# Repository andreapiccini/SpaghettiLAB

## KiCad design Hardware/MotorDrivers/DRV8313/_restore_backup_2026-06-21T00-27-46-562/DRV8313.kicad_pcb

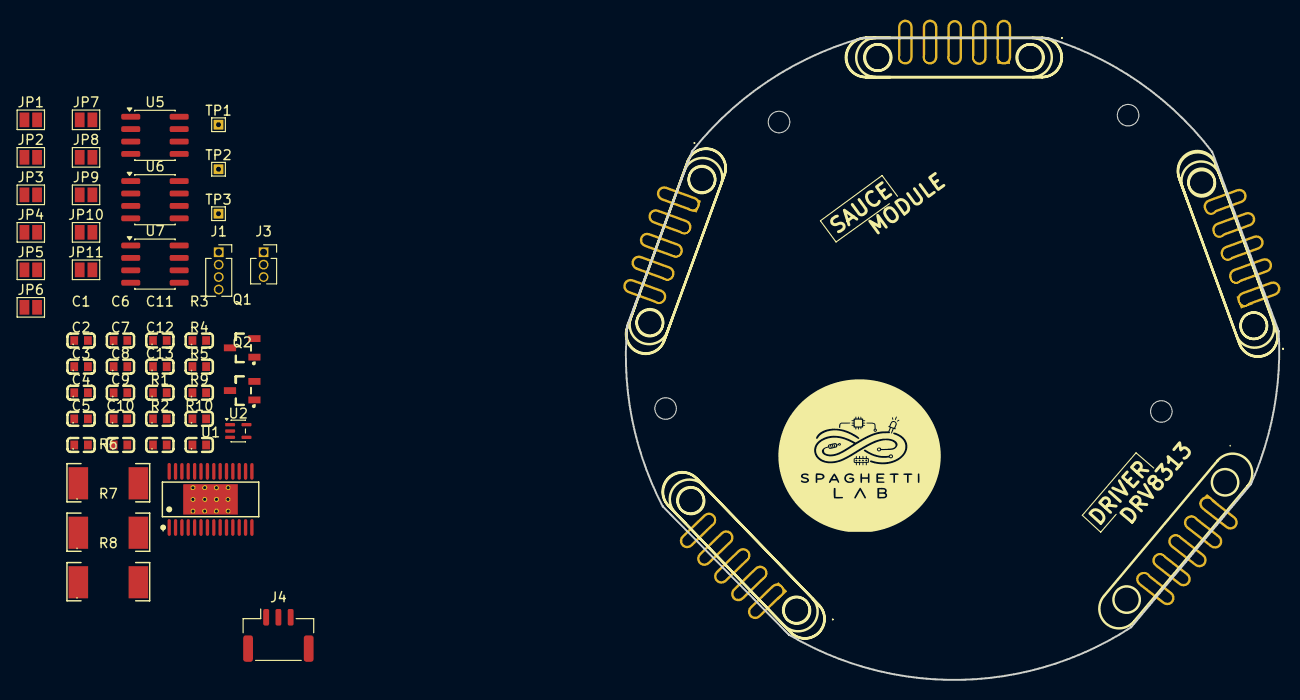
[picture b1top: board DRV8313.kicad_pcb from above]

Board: 2 copper layers, 66.8 x 65.6 mm, 61 parts (1 on the bottom side), 42 nets, no tracks yet.

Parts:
C1: 10nF; C0603
C2, C5, C6, C7, C8, C9, C11, C12, C13: 100nF; C0603
C3: 470nF; C0603
C4: 10uF; C0603
C10: 1uF; C0603
CN7, CN8, CN9, CN10, CN11: PR5L4015-5P-C-F; CONN-TH_PR5L4015-5P-C-F
H1, H2, H3, H4: MountingHole; MountingHole_2.2mm_M2
J1: Conn_01x04_Socket; PinSocket_1x04_P1.27mm_Vertical
J3: Conn_01x02_Socket; PinSocket_1x03_P1.27mm_Vertical
J4: Conn_01x03_Socket; JST_GH_SM03B-GHS-TB_1x03-1MP_P1.25mm_Horizontal
JP1, JP2: Jumper_2_Open; SolderJumper-2_P1.3mm_Open_Pad1.0x1.5mm
JP3, JP4, JP5, JP6, JP7, JP8, JP9, JP10, JP11: SolderJumper_2_Open; SolderJumper-2_P1.3mm_Open_Pad1.0x1.5mm
Q1, Q2: BSS123_C427379; SOT-23-3_L2.9-W1.5-P1.90-LS2.6-BR
R1, R2, R3, R4, R5, R10: 10k; C0603
R6, R7, R8: 10m; RES-SMD_L6.4-W3.2-R2512
R9: 1k; C0603
TP1, TP2, TP3: TestPoint_Flag; TestPoint_THTPad_1.0x1.0mm_Drill0.5mm
U1: MS8313; HTSSOP-28_L9.7-W4.4-P0.65-LS6.4-BL-EP
U2: TLV9001IDCK; SOT-353_SC-70-5
U5, U6, U7: INA241A2xD; SOIC-8_3.9x4.9mm_P1.27mm
U35, U36, U37, U38, U39: PR5L5015-5P-C-H; CONN-TH_PR5L5015-5P-C-H

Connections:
5V: CN8.5, U35.5
+3.3V: C3.2, JP4.2 (B), R1.1, R3.2, R4.2, R5.2, R10.2, U1.15 (V3P3OUT), U2.5 (V+)
/FLEX0: CN10.2, JP8.1 (A), U37.2
/FLEX1: CN10.3, JP9.1 (A), U37.3
/FLEX2: CN7.1, JP10.1 (A), U38.1
/FLEX3: CN7.2, JP5.1 (A), U38.2
/FLEX4: CN7.3, JP6.1 (A), U38.3
/FLEX5: CN9.1, JP7.1 (A), U36.1
/FLEX6: CN11.4, JP11.1 (A), U39.4
/ID: CN10.1, U37.1
/OUT_SENSE1: R6.1, TP1.1 (1_1), U1.5 (OUT1), U5.8 (+)
/OUT_SENSE2: R7.1, TP2.1 (1_1), U1.8 (OUT2), U6.8 (+)
/OUT_SENSE3: R8.1, TP3.1 (1_1), U1.9 (OUT3), U7.8 (+)
/REF: C10.1, JP1.2 (B), JP2.1 (A), R1.2, R2.1, U2.1 (+)
/REF_B: C11.1, C12.1, C13.1, J3.1, JP2.2 (B), U2.3 (-), U2.4, U5.3 (REF2), U5.7 (REF1), U6.3 (REF2), U6.7 (REF1), U7.3 (REF2), U7.7 (REF1)
/SCL_AUX: CN8.3, U35.3
/SDA_AUX: CN8.4, U35.4
/~INT: CN9.2, U36.2
/~RESET: CN9.3, Q1.1 (G), U36.3
C_SENSE1: JP5.2 (B), U5.5
C_SENSE2: JP6.2 (B), U6.5
C_SENSE3: JP7.2 (B), U7.5
EN: JP11.2 (B), R9.2
GND: C3.1, C4.2, C5.2, C6.1, C7.1, C8.1, C9.1, C10.2, C11.2, C12.2, C13.2, CN7.5, CN8.2, CN9.5, CN10.5, CN11.2, J1.4, J3.2, JP1.1 (A), Q1.2 (S), Q2.2 (S), R2.2, U1.6 (PGND1), U1.7 (PGND2), U1.10 (PGND3), U1.12 (COMPP), U1.13 (COMPN), U1.14 (GND), U1.19 (nCOMP0), U1.20 (GND), U1.21 (NC), U1.28 (GND), U1.29 (EP), U2.2 (V-), U5.2 (GND), U5.4 (GND), U6.2 (GND), U6.4 (GND), U7.2 (GND), U7.4 (GND), U35.2, U36.5, U37.5, U38.5, U39.2
IN1: JP8.2 (B), U1.27 (IN1)
IN2: JP9.2 (B), U1.25 (IN2)
IN3: JP10.2 (B), U1.23 (IN3)
unnamed: Q1.3 (D), Q2.1 (G), R10.1
unnamed: C1.2, U1.1 (CP1)
unnamed: C1.1, U1.2 (CP2)
unnamed: R9.1, U1.22 (EN3), U1.24 (EN2), U1.26 (EN1)
unnamed: C2.2, U1.3 (VCP)
OUT1: J4.1, R6.2, U5.1 (-)
OUT2: J4.2, R7.2, U6.1 (-)
OUT3: J4.3, R8.2, U7.1 (-)
VCC: C2.1, C4.1, C5.1, C6.2, C7.2, C8.2, C9.2, JP3.2 (B), U1.4 (VM), U1.11 (VM), U5.6 (V+), U6.6 (V+), U7.6 (V+)
VEXT: CN7.4, CN8.1, CN9.4, CN10.4, CN11.1, JP3.1 (A), U35.1, U36.4, U37.4, U38.4, U39.1
VHV: CN11.5, U39.5
VLOGIC: CN11.3, JP4.1 (A), U39.3
nFAULT: J1.3, R5.1, U1.18 (nFAULT)
nRESET: J1.1, Q2.3 (D), R3.1, U1.16 (nRESET)
nSLEEP: J1.2, R4.1, U1.17 (nSLEEP)

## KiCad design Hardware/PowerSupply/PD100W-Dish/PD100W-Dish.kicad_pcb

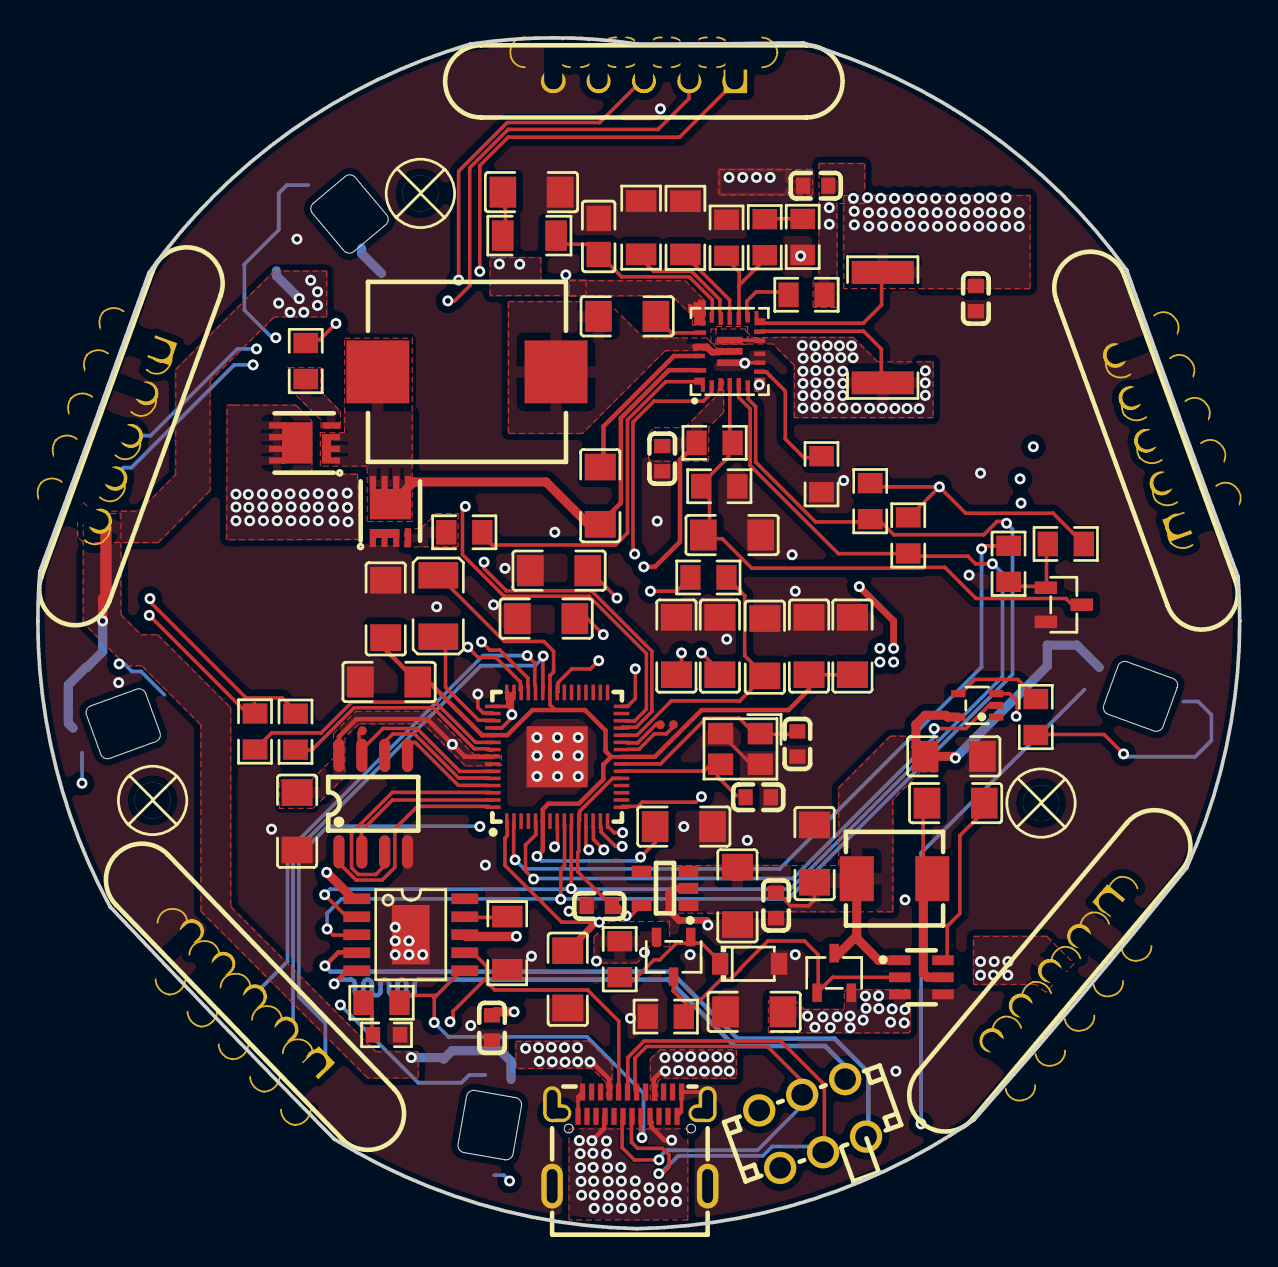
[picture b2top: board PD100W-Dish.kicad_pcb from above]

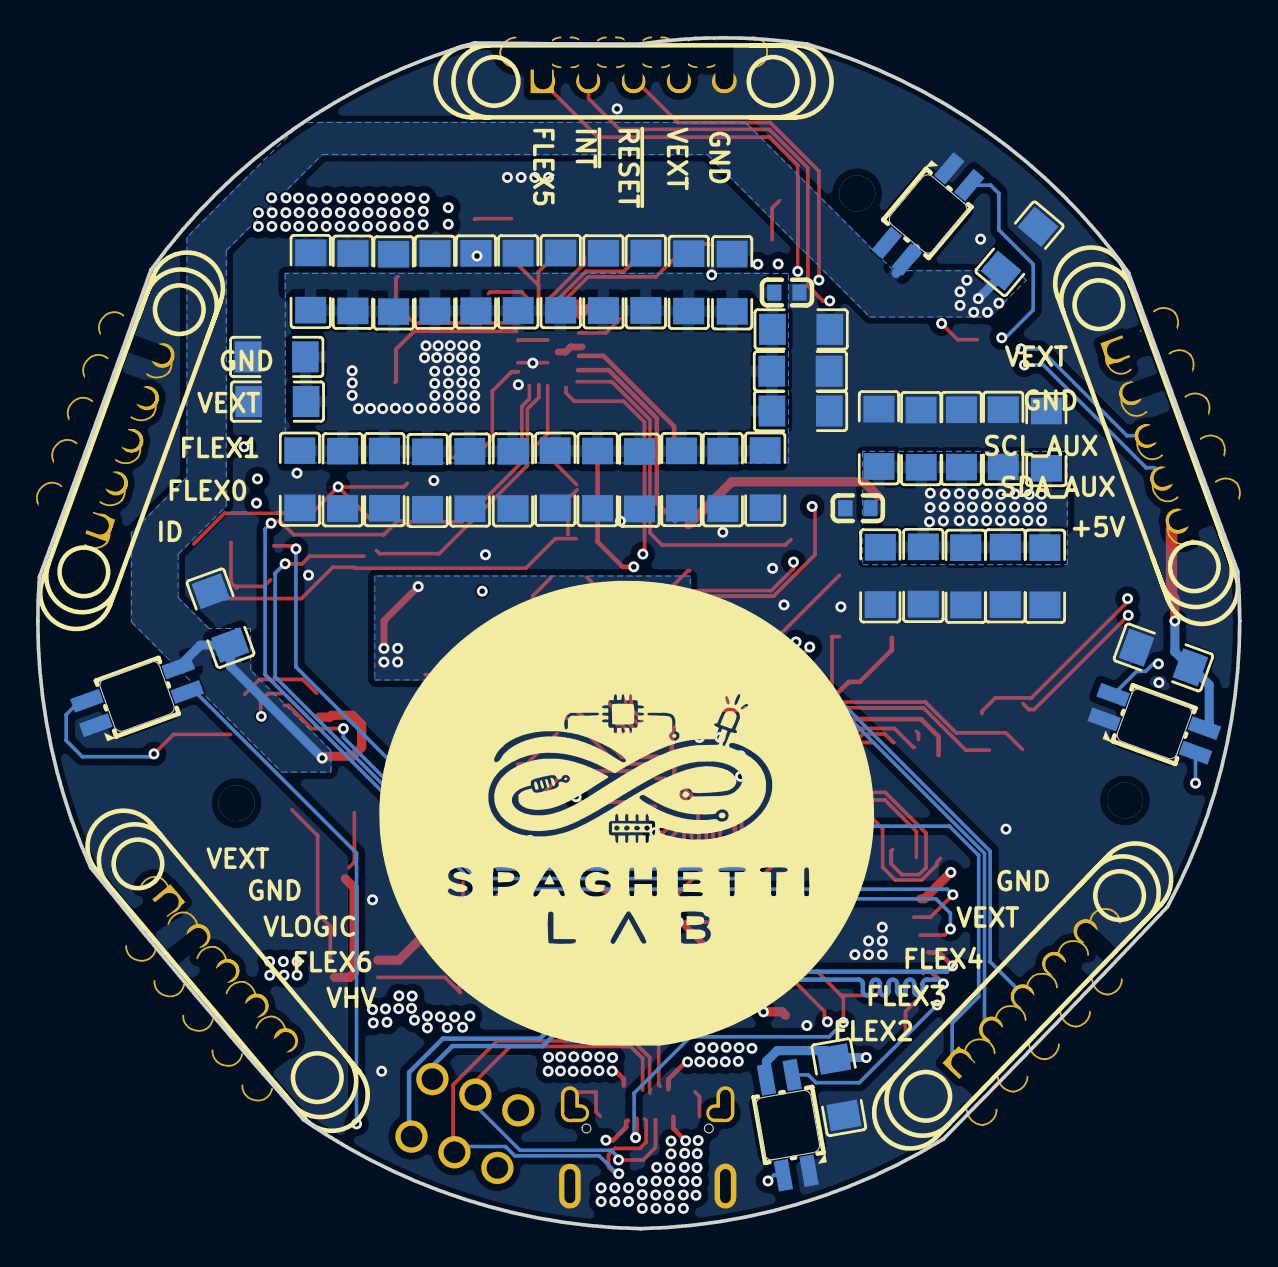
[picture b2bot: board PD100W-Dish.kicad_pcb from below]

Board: 4 copper layers, 66.8 x 66.2 mm, 139 parts (53 on the bottom side), 75 nets.

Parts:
C1, C2, C3, C4, C5, C6, C7, C8, C9, C10, C11, C12, C13, C14, C15, C16, C17, C25, C26, C27, C28, C29, C30, C32, C33, C40, C42, C54, C56, C57, C58, C61, C62, C67, C68, C70, C71, C72, C73, C74, C76, C81, C82, C87, C88, C89, C90, C91, C92, C93, C94, C95, C96, C97, C98, C99, C100, C101, C102, C103, C104, C109, C110: C1206
C24, C34, C35, C36, C37, C38, C43, C44, C65, C66: C0603
C41: C0805
CN7, CN8, CN9, CN10, CN11: CONN-TH_PR5L4015-5P-C-F
D1: SOD-123_L2.7-W1.6-LS3.7-RD
L4: L1210
L5: IND-SMD_L11.0-W10.0
L7: IND-SMD_L5.4-W5.2_FXL05XX
LED1, LED2, LED7, LED8: LED-SMD_4P-L3.2-W2.8-LS5.9_SK6812MINI-E
Q3: SOT-23-3_L2.9-W1.3-P1.90-LS2.4-BR
Q4, Q5: SOT-23-3_L3.0-W1.7-P0.95-LS2.9-BR
R20, R29, R30, R31, R32, R33, R34, R35, R36, R37, R38, R39, R40, R44, R45, R48, R49, R60, R61, R64: R0805
R21, R25, R26, R27: R1206
R46: R2512
R47: R0603
SCREW1, SCREW3, SCREW4: Screw-Hole-M2
SW1: SW-TH_K3-2245D-F1
TP1, TP2, TP4: Test-Point-0.5mm
U7: VQFN-HR-26_L4.0-W3.5_TPS55288RPMR
U8, U9: TSDSON-8-FL_L3.3-W3.3-P0.65-BL
U15: TSOT-23-6_L2.9-W1.6-P0.95-LS2.8-BL
U16: SOT-25-5_L2.9-W1.6-P0.95-LS2.8-BL
U17: QFN-60_L7.0-W7.0-P0.40-TL-EP3.4
U19: SOP-8_L4.9-W3.9-P1.27-LS6.0-BL
U33: SOT-353_L2.2-W1.4-P0.65-LS2.4-BR
U35, U36, U37, U38, U39: CONN-TH_PR5L5015-5P-C-H
U40: ESSOP-10_L4.9-W3.9-P1.0-LS6.0-TL-EP
USB4: USB-C-SMD_TYPEC-324G-BCP24
X1: CRYSTAL-SMD_4P-L3.2-W2.5-BL

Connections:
1V1: C70.1, C71.1, C72.1, C73.1, C74.1, L4.2, U17.6, U17.23, U17.39, U17.50
5V: C65.2, C81.2, C82.2, C102.1, C103.1, C104.1, C109.1, C110.1, CN8.5, L7.2, LED1.3, LED2.3, LED7.3, LED8.3, Q4.3, U15.1, U16.1, U16.3, U33.5, U35.5
$1N8973: R45.1, U7.2
$1N8976: R45.2, U8.4
$1N8978: R44.2, U9.4
$1N8980: R44.1, U7.1
$1N9027: C32.1, U7.20
$1N9029: C40.1, U7.22
$1N9105: R25.2, U7.16
$1N9112: R26.2, U7.17
$1N9115: C41.2, R27.2, U7.18
$1N9120: C42.2, R27.1
$1N9155: R30.2, U7.8
$1N9158: C33.2, Q3.3, R31.1, R32.2, U7.4
$1N9180: Q3.1, R33.1, R34.1
$1N24858: R29.2, U7.14
$1N24894: R20.1, R60.2
$1N24900: R20.2, R38.2, U7.15
$2N2987: TP1.1, U17.25
$2N2988: TP2.1, U17.24
$2N2989: C57.1, R37.1, U17.26
$2N2992: C44.1, U17.22, X1.1
$2N2993: C43.1, U17.21, X1.3
$2N3073: R39.1, U17.52
$2N3074: R40.1, U17.51
$2N3076: L4.1, U17.48
$2N5930: LED7.4, LED8.2
$2N6872: R61.2, U33.4
$2N6876: LED7.2, R61.1
$2N14399: LED2.2, LED8.4
$2N14400: LED1.2, LED2.4
$3N1781: R21.1, U40.9
$3N1785: C62.2, U15.6
$3N1787: C62.1, L7.1, U15.5
$3N1801: R47.2, R64.1
$3N1804: Q4.1, Q5.3, R48.1, U15.2
$3N1806: D1.1, Q5.1, R49.2
ADD_LED: U17.5, U33.2
AGND: C1.1, C2.1, C3.1, C4.1, C5.1, C6.1, C7.1, C8.1, C9.1, C10.1, C11.1, C12.1, C13.1, C14.1, C15.1, C16.1, C17.1, C24.1, C25.1, C26.1, C27.2, C28.2, C29.2, C30.2, C33.1, C34.1, C35.1, C36.1, C37.1, C38.1, C41.1, C42.1, C43.2, C44.2, C54.1, C56.1, C57.2, C58.1, C61.1, C65.1, C66.1, C67.1, C68.1, C70.2, C71.2, C72.2, C73.2, C74.2, C76.2, C81.1, C82.1, C87.1, C88.1, C89.1, C90.1, C91.1, C92.1, C93.1, C94.1, C95.1, C96.1, C97.1, C98.1, C99.1, C100.1, C101.1, C102.2, C103.2, C104.2, C109.2, C110.2, CN7.5, CN8.2, CN9.5, CN10.5, CN11.2, D1.2, LED1.1, LED2.1, LED7.1, LED8.1, Q3.2, R21.2, R25.1, R26.1, R30.1, R32.1, R38.1, R47.1, R48.2, R60.1, U7.7, U7.9, U7.10, U7.24, U9.1, U9.2, U9.3, U15.4, U16.2, U17.47, U17.61, U19.4, U33.3, U35.2, U36.5, U37.5, U38.5, U39.2, U40.11, USB4.1, USB4.2, USB4.3, USB4.4, USB4.A1, USB4.A12, USB4.B1, USB4.B12, X1.2, X1.4
EN_PSOUT: R34.2, U17.2
FLEX0: CN10.2, U17.14, U37.2
FLEX1: CN10.3, U17.15, U37.3
FLEX2: CN7.1, U17.43, U38.1
FLEX3: CN7.2, U17.40, U38.2
FLEX4: CN7.3, U17.41, U38.3
FLEX5: CN9.1, U17.42, U36.1
FLEX6: CN11.4, U17.16, U39.4
ID: CN10.1, U17.13, U37.1
INT_N: CN9.2, U17.8, U36.2
IOSN+2: C1.2, C2.2, C3.2, C4.2, C5.2, C6.2, C7.2, C8.2, C9.2, C10.2, C11.2, C12.2, C27.1, C28.1, C29.1, C30.1, C35.2, C87.2, C88.2, C89.2, C90.2, C91.2, C92.2, C93.2, C94.2, C95.2, C96.2, C97.2, C98.2, R46.1, U7.11, U7.12, U7.26
QSPI_SCLK: U17.56, U19.6
QSPI_SD0: U17.57, U19.5
QSPI_SD1: U17.59, U19.2
QSPI_SD2: U17.58, U19.3
QSPI_SD3: TP4.1, U17.55, U19.7
QSPI_SS: U17.60, U19.1
RESET_N: CN9.3, U17.12, U36.3
SCL_AUX: CN8.3, U17.28, U35.3
SCL_PW: R36.2, U7.5, U17.10, U40.2
SDA_AUX: CN8.4, U17.27, U35.4
SDA_PW: R35.2, U7.6, U17.9, U40.3
SW12: C40.2, L5.1, U7.23, U8.1, U8.2, U8.3, U9.5, U9.6, U9.7, U9.8
SW22: C32.2, L5.2, U7.21, U7.25
SW_NA_DN: R40.2, SW1.3
SW_NA_DP: R39.2, SW1.4
SW_NC_DN: SW1.1, U40.5
SW_NC_DP: SW1.6, U40.4
USBC_CC1: U40.7, USB4.A5
USBC_CC2: R64.2, U40.6, USB4.B5
USBC_DN: SW1.2, USB4.A7, USB4.B7
USBC_DP: SW1.5, USB4.A6, USB4.B6
VCC: C38.2, R29.1, U7.19
VEXT: C36.2, CN7.4, CN8.1, CN9.4, CN10.4, CN11.1, R46.2, U7.13, U35.1, U36.4, U37.4, U38.4, U39.1
VHV: C13.2, C14.2, C15.2, C16.2, C17.2, C24.2, C25.2, C26.2, C34.2, C37.2, C61.2, C99.2, C100.2, C101.2, CN11.5, Q4.2, Q5.2, R31.2, R49.1, U7.3, U8.5, U8.6, U8.7, U8.8, U15.3, U39.5, U40.1, U40.8, USB4.A4, USB4.A9, USB4.B4, USB4.B9
VLOGIC: C54.2, C56.2, C58.2, C66.2, C67.2, C68.2, C76.1, CN11.3, R33.2, R35.1, R36.1, R37.2, U16.5, U17.1, U17.11, U17.20, U17.30, U17.38, U17.44, U17.45, U17.46, U17.49, U17.53, U17.54, U19.8, U39.3
